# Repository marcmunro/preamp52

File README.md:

# Pre-Amp 52

This is a hifi pre-amp that takes 5 channel surround sound and mixes
it down to stereo.

It is designed to be part of a hifiberry and chromecast TV based sound
system that looks something like this:

    +------------+
    |            |           +-----------+
    | Chromecast |           | hifiberry |--------+
    |            |           +-----------+        |
    +------------+                     | Stereo   |
          |                            +------+   |
          | hdmi                              |   |Control
         \|/                                  |   |
    +----------------------+  5-channel audio |   |
    | hdmi to analog audio |------+           |   |
    +----------------------+      |     +-----+   |
          |                       |     |         |
          | hdmi                  |     |         |
         \|/                     \|/   \|/       \|/
    +-----------+            +-------------------------+     
    |           |            |                         |
    |    TV     |            |       Pre-Amp 52        |
    |           |            |                         |
    +-----------+            +-------------------------+
                                 |               |  
                                 |               |  
                                 |               |  
                                \|/             \|/
                +----------------------+  +----------------------+
                |   Stereo Amplifier   |  |  Headphone Amplifier |
                +----------------------+  +----------------------+

The reason for doing all this, is that a lot of programming has poor
stereo mixing.  Being able to separately control the mix amplitude for
the centre channel in particular can greatly improve the listening
experience (you may even be able to understand some of the dialog).

Note that the Rpi based hifiberry provides all of the control for the
pre-amp.  This includes switching from TV to hifi sources, managing
the relative volumes of the centre, front and rear channels, and
overall volume.

## Contents

The `kicad` directory contains kicad6 files for the circuit.  A PDF of
the schematic is provided as `schematic.pdf`.  Note that there are 2
pages.

Gerber files for pcb generation can be found in `kicad/pcb`.

## Circuit Overview

### Input Selection and 5 Channel to 2 Downmixer

Stereo input, in my case from a Rasperry Pi-based hifiberry is
provided from J1 and J7 (in my case these are hard-soldered as the
hifiberry is in the same case as the preamp).  All inputs are
AC-coupled via 1μF capacitors.  Depending on your sources it may be
possible to use DC coupling and eliminate thses capacitors.

5-channel input is provided by J2 to J6.  J4, the centre input feeds 2
operational amplifiers configured as non-inverting buffer amplifiers.
These are present to eliminate cross-talk in the passive mixer stage
comprsising U2, U3 and U4, which are audio quality stereo digital
potentiometers and mix the 5 channel input into two channel stereo
with the centre channel being fed to both stereo channels.

This mixer stage allows independent attenuation of the front, centre
and rear channels.

A latching relay switches between the stereo input and the downmixed 5
channel input.

### Buffer Amplifier Stage

The pair of unity-gain non-inverting buffer amplifiers formed from U5
take the selected input and feed it to the tape (or in my case,
headphone) output and to the master volume control stage.

Using buffer amps here eliminates any impedence matching issues
between the input sources and the digital potentiometer U6.  

The OPA2134 op-amps are high quality audio components and should add
no noticable noise or distortion to the signal path.

### Master Volume Control Stage

Buffered signal inputs feed U6, another audio quality digital
potentiometer which provides the master volume control.  Output from
this is fed through a final unity-gain non-inverting buffer amplifier,
U7, which provides a low impedence output to drive an amplifier.  As
with the input stages, it may be possible to eliminate the decoupling
capacitors, depending on your setup.

### Power Supply

The power supply takes a single 12V supply and provides plus and minus
7V supplies to drive the opamps, and +7V for the digital
potentiometers.  The +5V needed by the digital potentiometers is
provided from the Raspberry Pi.

U8 is a DC-DC converter, that provides an isolated 12V supply from a
12V input.  This isolated supply, is used to provide -12V to R38, D4,
Q4 and R42 forming a primitive but good enough voltage regulator for
the -7V supply.  C21 further smooths this supply rail.

R39, D3, Q3 and R41 form another voltage regulator, this time on the
positive side.  C20 smooths this supply.

### Relay Drivers

R37 and Q1, and R40 and Q2, each provide relay drivers to switch K1
between the 5-channel and stereo inputs.  These are driven from
Raspberry Pi GPIO pins.  Note that as the relay is a latching type,
only a short pulse is required to switch the relay one way or the
other.

### Digital Potentiometer Controls

The 4 digital potentiometers that control the 5-channel downmixer and
volume, are all controlled from the I2C bus input from the Raspberry
Pi.

Each potentiometer has its own address on the bus with: U4, controlling
the centre channel, having address 0; U3, controlling the rear
channels, address 1; U2 controlling the front channels, address 2; and 
U6, the master volume, address 3.

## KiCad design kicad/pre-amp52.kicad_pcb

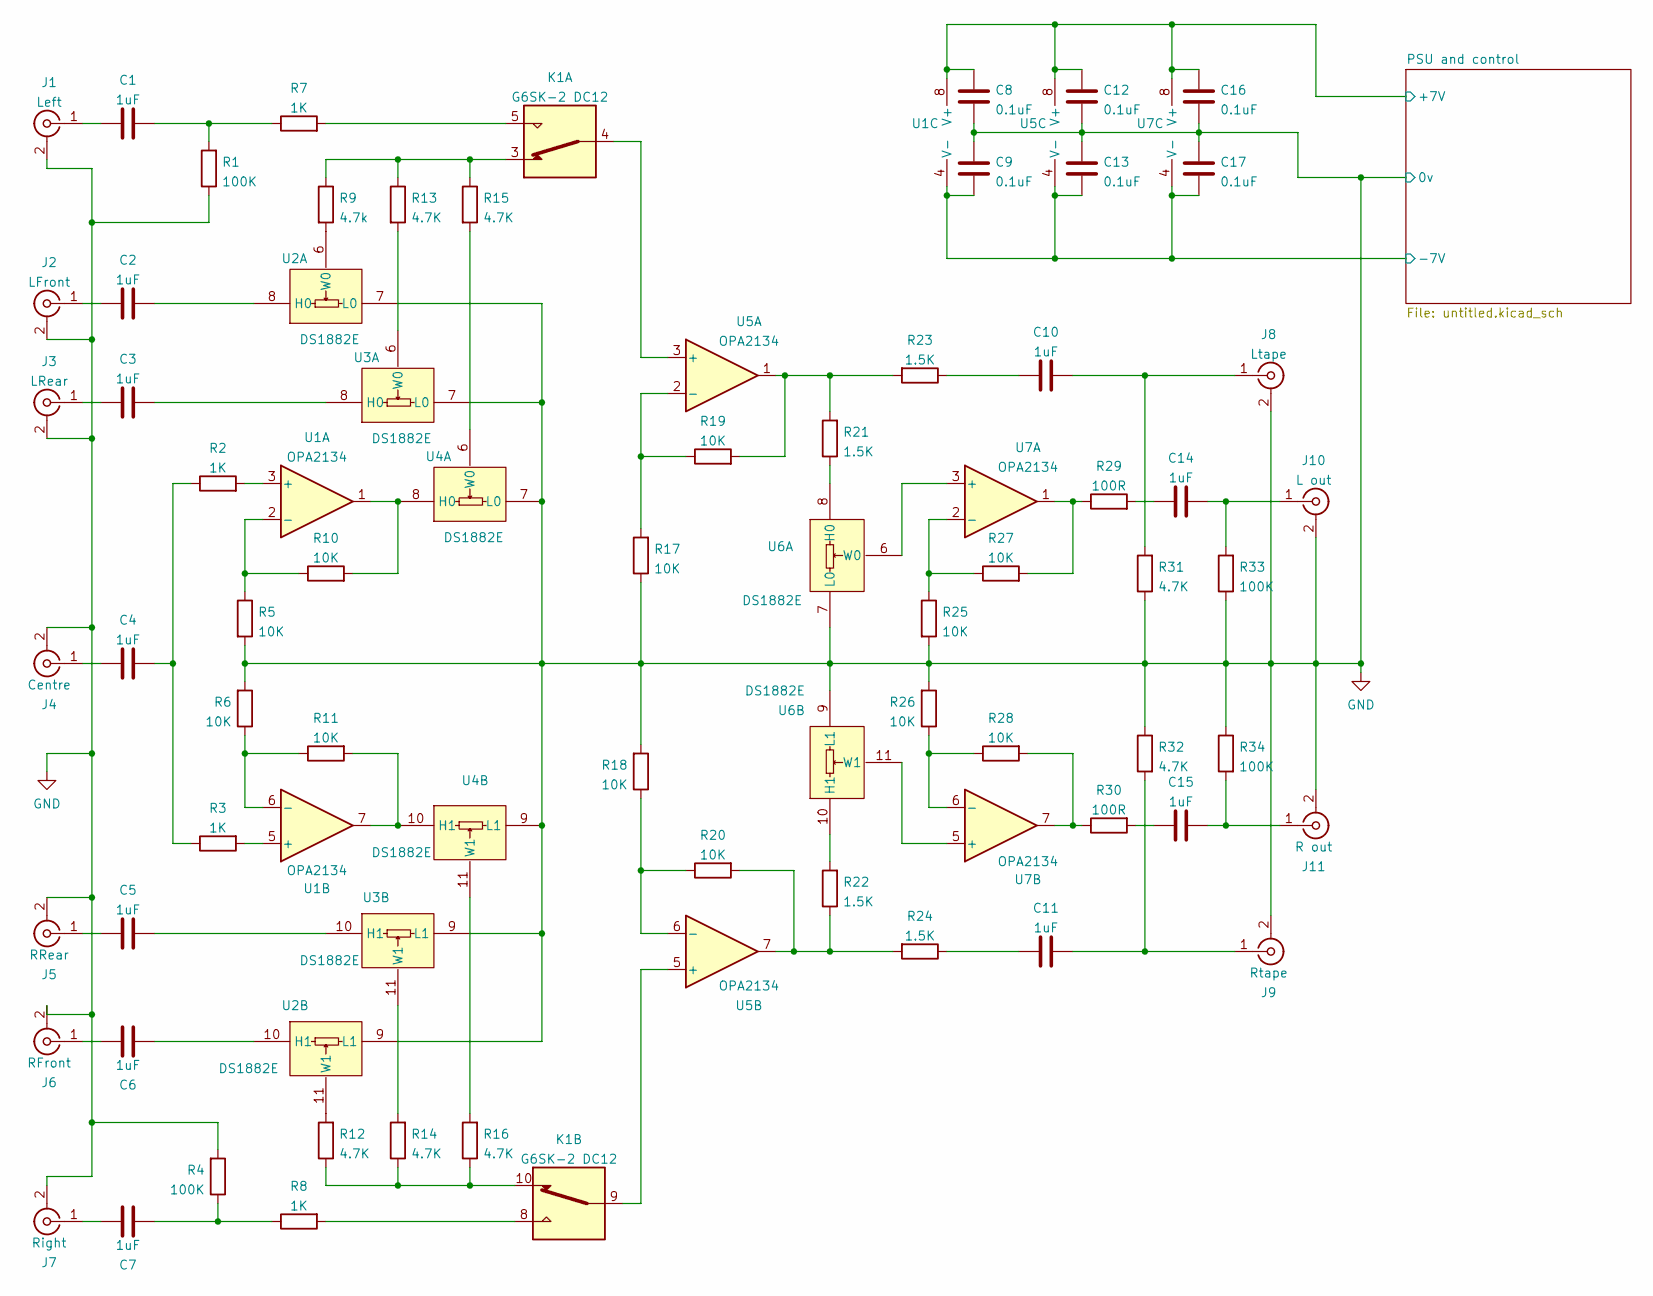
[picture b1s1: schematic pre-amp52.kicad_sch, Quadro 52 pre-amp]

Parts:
C1, C2, C3, C4, C5, C6, C7, C10, C11, C14, C15: 1uF; C_Disc_D7.0mm_W2.5mm_P5.00mm
C8, C9, C12, C13, C16, C17: 0.1uF; C_0603_1608Metric_Pad1.08x0.95mm_HandSolder
J1: Left; SolderWire-0.1sqmm_1x02_P3.6mm_D0.4mm_OD1mm
J2: LFront; SolderWire-0.1sqmm_1x02_P3.6mm_D0.4mm_OD1mm
J3: LRear; SolderWire-0.1sqmm_1x02_P3.6mm_D0.4mm_OD1mm
J4: Centre; SolderWire-0.1sqmm_1x02_P3.6mm_D0.4mm_OD1mm
J5: RRear; SolderWire-0.1sqmm_1x02_P3.6mm_D0.4mm_OD1mm
J6: RFront; SolderWire-0.1sqmm_1x02_P3.6mm_D0.4mm_OD1mm
J7: Right; SolderWire-0.1sqmm_1x02_P3.6mm_D0.4mm_OD1mm
J8: Ltape; SolderWire-0.1sqmm_1x02_P3.6mm_D0.4mm_OD1mm
J9: Rtape; SolderWire-0.1sqmm_1x02_P3.6mm_D0.4mm_OD1mm
J10: L out; SolderWire-0.1sqmm_1x02_P3.6mm_D0.4mm_OD1mm
J11: R out; SolderWire-0.1sqmm_1x02_P3.6mm_D0.4mm_OD1mm
K1: G6SK-2 DC12; Relay_DPDT_Kemet_EC2_DoubleCoil
R1, R4, R33, R34: 100K; R_Axial_DIN0207_L6.3mm_D2.5mm_P10.16mm_Horizontal
R2, R3, R7, R8: 1K; R_Axial_DIN0207_L6.3mm_D2.5mm_P10.16mm_Horizontal
R5, R6, R10, R11, R17, R18, R19, R20, R25, R26, R27, R28: 10K; R_Axial_DIN0207_L6.3mm_D2.5mm_P10.16mm_Horizontal
R9: 4.7k; R_Axial_DIN0207_L6.3mm_D2.5mm_P10.16mm_Horizontal
R12, R13, R14, R15, R16, R31, R32: 4.7K; R_Axial_DIN0207_L6.3mm_D2.5mm_P10.16mm_Horizontal
R21, R22, R23, R24: 1.5K; R_Axial_DIN0207_L6.3mm_D2.5mm_P10.16mm_Horizontal
R29, R30: 100R; R_Axial_DIN0207_L6.3mm_D2.5mm_P10.16mm_Horizontal
U1, U5, U7: OPA2134; DIP-8_W10.16mm
U2, U3, U4, U6: DS1882E; TSSOP-16_4.4x5mm_P0.65mm

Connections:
/PSU and control/+7V: C8.1, C12.1, C16.1, U1.8 (V+), U5.8 (V+), U7.8 (V+); also elsewhere on the board
/PSU and control/-7V: C9.2, C13.2, C17.2, U1.4 (V-), U5.4 (V-), U7.4 (V-); also elsewhere on the board
GND: C8.2, C9.1, C12.2, C13.1, C16.2, C17.1, J1.2 (Ext), J2.2 (Ext), J3.2 (Ext), J4.2 (Ext), J5.2 (Ext), J6.2 (Ext), J7.2 (Ext), J8.2 (Ext), J9.2 (Ext), J10.2 (Ext), J11.2 (Ext), R1.1, R4.2, R5.2, R6.2, R17.1, R18.2, R25.2, R26.2, R31.1, R32.1, R33.1, R34.1, U2.7 (L0), U2.9 (L1), U3.7 (L0), U3.9 (L1), U4.7 (L0), U4.9 (L1), U6.7 (L0), U6.9 (L1); also elsewhere on the board
unnamed: C1.1, J1.1 (In)
unnamed: C1.2, R1.2, R7.1
unnamed: C2.1, J2.1 (In)
unnamed: C2.2, U2.8 (H0)
unnamed: C3.1, J3.1 (In)
unnamed: C3.2, U3.8 (H0)
unnamed: C4.1, J4.1 (In)
unnamed: C4.2, R2.1, R3.1
unnamed: C5.1, J5.1 (In)
unnamed: C5.2, U3.10 (H1)
unnamed: C6.1, J6.1 (In)
unnamed: C6.2, U2.10 (H1)
unnamed: C7.1, J7.1 (In)
unnamed: C7.2, R4.1, R8.1
unnamed: C10.1, R23.1
unnamed: C10.2, J8.1 (In), R31.2
unnamed: C11.1, R24.1
unnamed: C11.2, J9.1 (In), R32.2
unnamed: C14.1, R29.2
unnamed: C14.2, J10.1 (In), R33.2
unnamed: C15.1, R30.2
unnamed: C15.2, J11.1 (In), R34.2
unnamed: K1.3, R9.1, R13.1, R15.1
unnamed: K1.4, U5.3 (+)
unnamed: K1.5, R7.2
unnamed: K1.8, R8.2
unnamed: K1.9, U5.5 (+)
unnamed: K1.10, R12.1, R14.1, R16.1
unnamed: R2.2, U1.3 (+)
unnamed: R3.2, U1.5 (+)
unnamed: R9.2, U2.6 (W0)
unnamed: R5.1, R10.1, U1.2 (-)
unnamed: R10.2, U1.1, U4.8 (H0)
unnamed: R6.1, R11.1, U1.6 (-)
unnamed: R11.2, U1.7, U4.10 (H1)
unnamed: R12.2, U2.11 (W1)
unnamed: R13.2, U3.6 (W0)
unnamed: R14.2, U3.11 (W1)
unnamed: R15.2, U4.6 (W0)
unnamed: R16.2, U4.11 (W1)
unnamed: R17.2, R19.1, U5.2 (-)
unnamed: R18.1, R20.1, U5.6 (-)
unnamed: R19.2, R21.2, R23.2, U5.1
unnamed: R20.2, R22.1, R24.2, U5.7
unnamed: R21.1, U6.8 (H0)
unnamed: R22.2, U6.10 (H1)
unnamed: R25.1, R27.1, U7.2 (-)
unnamed: R26.1, R28.1, U7.6 (-)
unnamed: R27.2, R29.1, U7.1
unnamed: R28.2, R30.1, U7.7
unnamed: U6.6 (W0), U7.3 (+)
unnamed: U6.11 (W1), U7.5 (+)

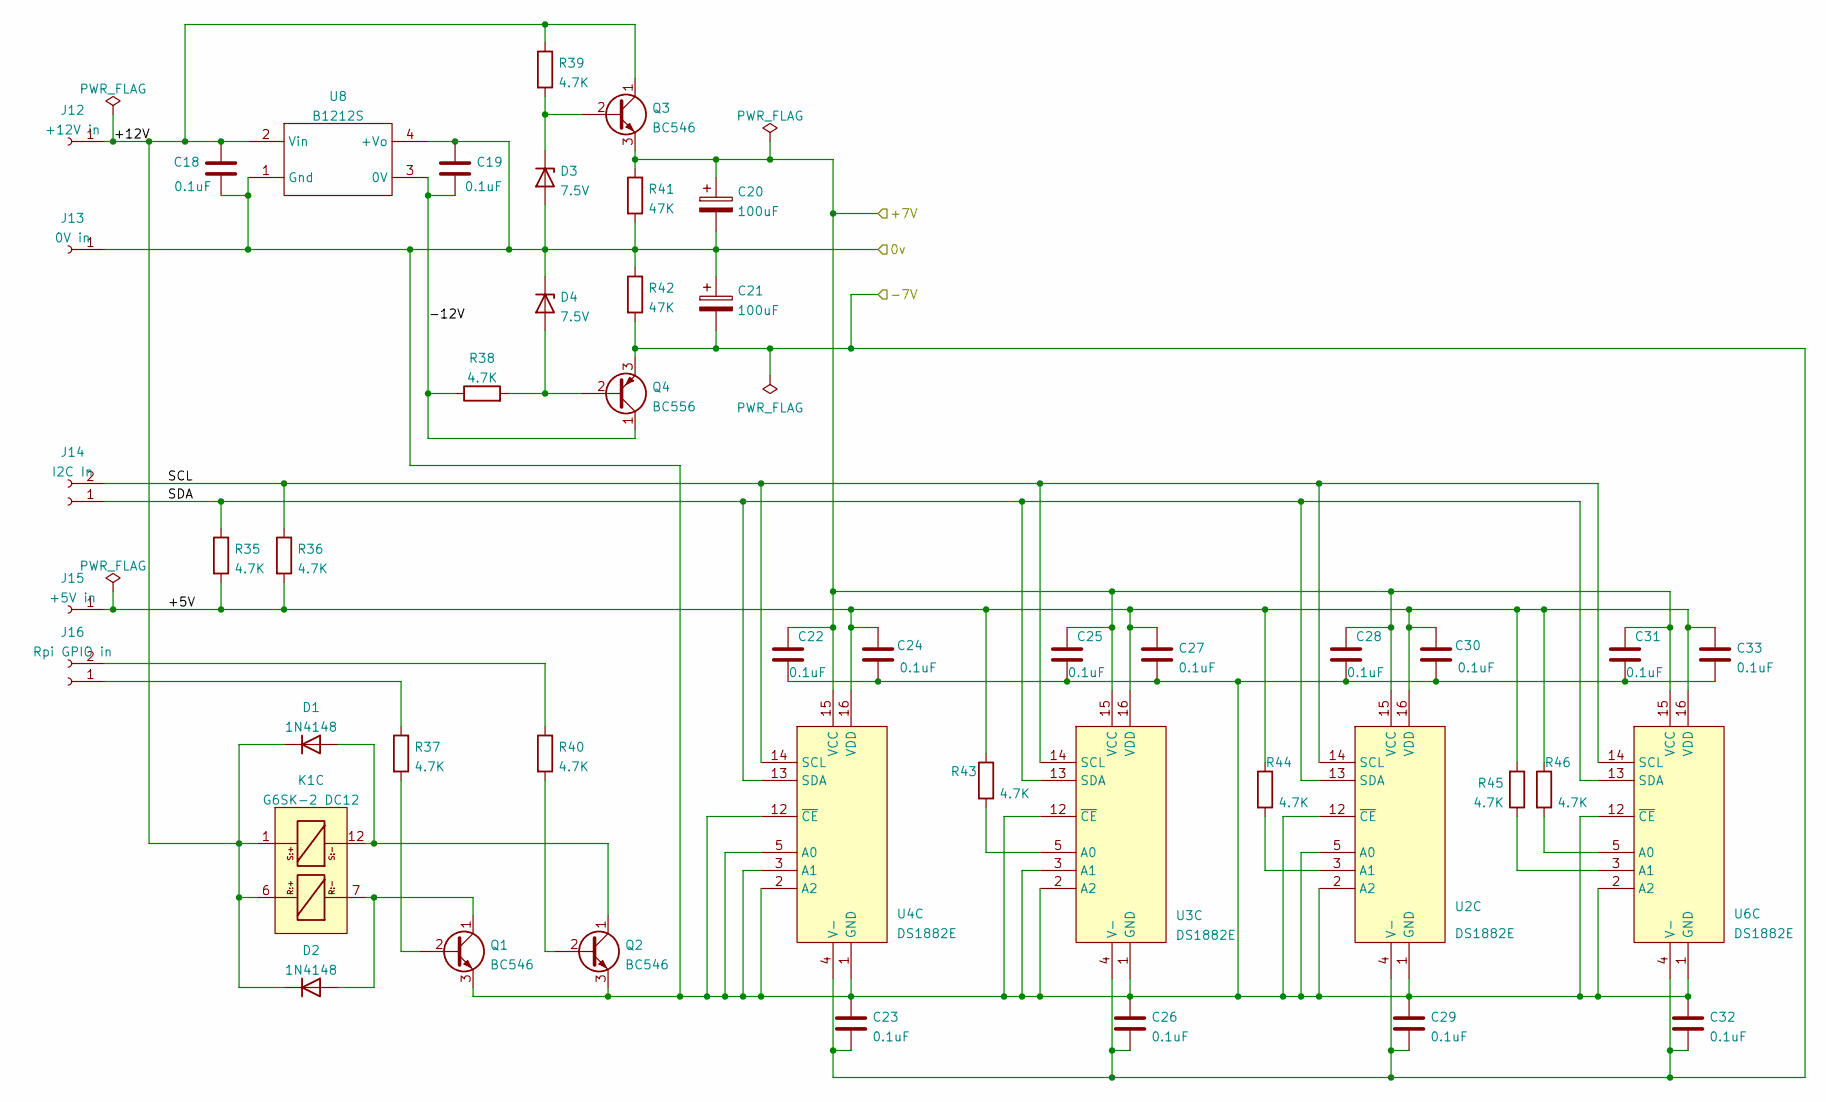
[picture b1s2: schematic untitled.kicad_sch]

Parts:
C18, C19, C22, C23, C24, C25, C26, C27, C28, C29, C30, C31, C32, C33: 0.1uF; C_0603_1608Metric_Pad1.08x0.95mm_HandSolder
C20, C21: 100uF; CP_Radial_D6.3mm_P2.50mm
D1, D2: 1N4148; D_DO-35_SOD27_P7.62mm_Horizontal
D3, D4: 7.5V; D_DO-35_SOD27_P10.16mm_Horizontal
J12: +12V in; SolderWire-0.5sqmm_1x01_D0.9mm_OD2.3mm
J13: 0V in; SolderWire-0.5sqmm_1x01_D0.9mm_OD2.3mm
J14: I2C In; SolderWire-0.1sqmm_1x02_P3.6mm_D0.4mm_OD1mm
J15: +5V in; SolderWire-0.5sqmm_1x01_D0.9mm_OD2.3mm
J16: Rpi GPIO in; SolderWire-0.1sqmm_1x02_P3.6mm_D0.4mm_OD1mm
K1: G6SK-2 DC12; Relay_DPDT_Kemet_EC2_DoubleCoil
Q1, Q2, Q3: BC546; TO-92_Inline
Q4: BC556; TO-92_Inline
R35, R36, R37, R38, R39, R40, R43, R44, R45, R46: 4.7K; R_Axial_DIN0207_L6.3mm_D2.5mm_P10.16mm_Horizontal
R41, R42: 47K; R_Axial_DIN0207_L6.3mm_D2.5mm_P10.16mm_Horizontal
U2, U3, U4, U6: DS1882E; TSSOP-16_4.4x5mm_P0.65mm
U8: B1212S; B212S

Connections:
/PSU and control/+5V: C24.1, C27.1, C30.1, C33.1, J15.1, R35.2, R36.2, R43.1, R44.1, R45.2, R46.1, U2.16 (VDD), U3.16 (VDD), U4.16 (VDD), U6.16 (VDD)
/PSU and control/+7V: C20.1, C22.1, C25.1, C28.1, C31.1, Q3.3 (E), R41.1, U2.15 (VCC), U3.15 (VCC), U4.15 (VCC), U6.15 (VCC); also elsewhere on the board
/PSU and control/+12V: C18.1, D1.1 (K), D2.1 (K), J12.1, K1.1, K1.6, Q3.1 (C), R39.1, U8.2 (Vin)
/PSU and control/-7V: C21.2, C23.2, C26.2, C29.2, C32.2, Q4.3 (E), R42.2, U2.4 (V-), U3.4 (V-), U4.4 (V-), U6.4 (V-); also elsewhere on the board
/PSU and control/-12V: C19.2, Q4.1 (C), R38.1, U8.3 (0V)
/PSU and control/SCL: J14.2, R36.1, U2.14 (SCL), U3.14 (SCL), U4.14 (SCL), U6.14 (SCL)
/PSU and control/SDA: J14.1, R35.1, U2.13 (SDA), U3.13 (SDA), U4.13 (SDA), U6.13 (SDA)
GND: C18.2, C19.1, C20.2, C21.1, C22.2, C23.1, C24.2, C25.2, C26.1, C27.2, C28.2, C29.1, C30.2, C31.2, C32.1, C33.2, D3.2 (A), D4.1 (K), J13.1, Q1.3 (E), Q2.3 (E), R41.2, R42.1, U2.1 (GND), U2.2 (A2), U2.5 (A0), U2.12 (~CE), U3.1 (GND), U3.2 (A2), U3.3 (A1), U3.12 (~CE), U4.1 (GND), U4.2 (A2), U4.3 (A1), U4.5 (A0), U4.12 (~CE), U6.1 (GND), U6.2 (A2), U6.12 (~CE), U8.1 (Gnd), U8.4 (+Vo); also elsewhere on the board
unnamed: D1.2 (A), K1.12, Q2.1 (C)
unnamed: D2.2 (A), K1.7, Q1.1 (C)
unnamed: D3.1 (K), Q3.2 (B), R39.2
unnamed: D4.2 (A), Q4.2 (B), R38.2
unnamed: J16.1, R37.1
unnamed: J16.2, R40.1
unnamed: Q1.2 (B), R37.2
unnamed: Q2.2 (B), R40.2
unnamed: R43.2, U3.5 (A0)
unnamed: R44.2, U2.3 (A1)
unnamed: R45.1, U6.3 (A1)
unnamed: R46.2, U6.5 (A0)

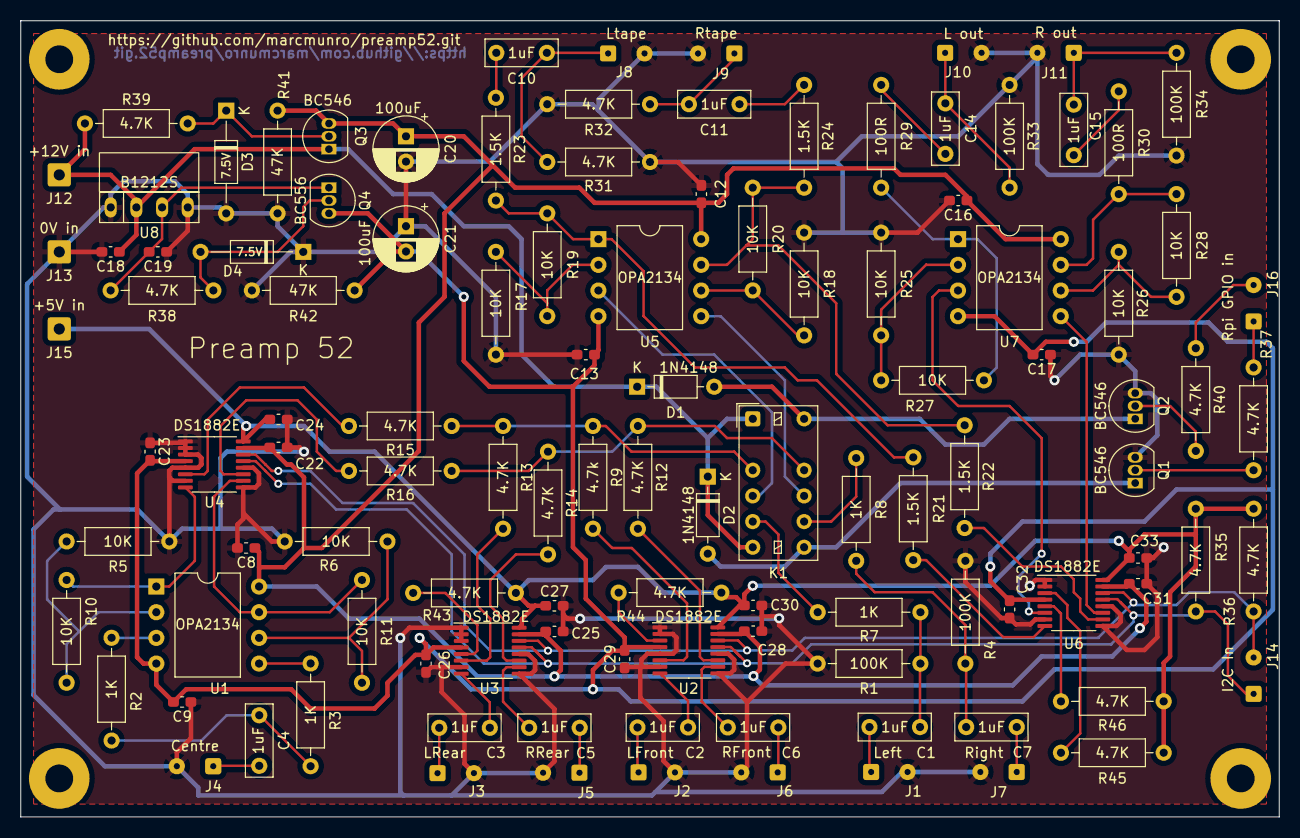
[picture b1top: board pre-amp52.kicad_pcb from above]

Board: 2 copper layers, 124.5 x 78.7 mm, 112 parts (0 on the bottom side), 72 nets.

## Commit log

2022-10-27 First release to github.
2022-10-27 Added github URLs to PCB
2022-10-28 Created schematic pdf and gerber files for pcb.
2022-10-29 Updated README with contents and circuit description.
